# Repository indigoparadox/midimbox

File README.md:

# midimbox

Simple MIDI adaptor box designed to connect to PC gameport

Notes:

- At present, output works, but input does not.
- TRS *or* DIN sockets may be used, but not both simultaneously.

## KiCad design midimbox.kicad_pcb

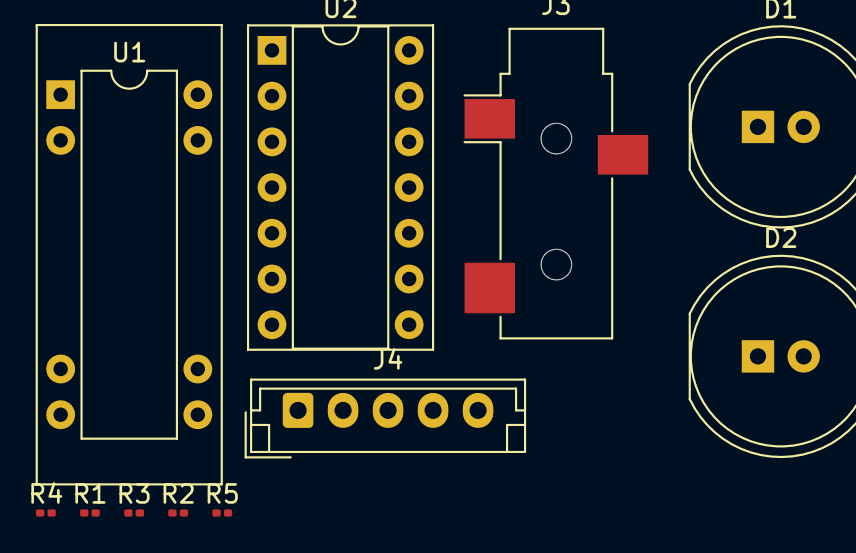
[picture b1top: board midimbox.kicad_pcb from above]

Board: 2 copper layers, 11 parts (0 on the bottom side), 13 nets, no tracks yet.

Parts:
D1, D2: LED; LED_D10.0mm
J3: AudioJack3; Jack_3.5mm_CUI_SJ-3523-SMT_Horizontal
J4: Conn_01x05; JST_EH_B5B-EH-A_1x05_P2.50mm_Vertical
R1, R2, R4: 220; R_0201_0603Metric
R3, R5: 4.7k; R_0201_0603Metric
U1: 6N138; DIP-8-16_W7.62mm_Socket
U2: 74LS00; DIP-14_W7.62mm_Socket

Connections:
unnamed: D1.1 (K), D2.1 (K), J3.S, J4.4, U1.5 (GND), U2.7 (GND)
unnamed: D1.2 (A), R3.2
unnamed: D2.2 (A), R5.1
unnamed: J3.T, R2.1
unnamed: J3.R, R4.2
unnamed: J4.1, R4.1, U1.8 (VCC), U2.14 (VCC)
unnamed: J4.2, U2.12, U2.13
unnamed: J4.3, U2.6
unnamed: R1.1, U1.2 (C1)
unnamed: R2.2, U2.8
unnamed: R3.1, U2.3, U2.4, U2.5
unnamed: R5.2, U2.9, U2.10, U2.11
unnamed: U1.6 (VO2), U2.1, U2.2

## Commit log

2022-05-29 Initial rough revision based on built box. Input doesn't work.
2022-05-29 Using CC-BY-SA 4.0.
2022-05-29 Added workbook and ignore file.
2022-05-29 Rough attempt at modelling the PCB.
